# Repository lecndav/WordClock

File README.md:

# Word Clock

This repository contains the source code of my Word Clock and some information about it.

## Order list

* Photo resistor: [Amazon](https://www.amazon.de/DealMux-GL5539-30K-90K-lichtabhängige-Fotowiderstände/dp/B01EZZMLOI/ref=sr_1_1?ie=UTF8&qid=1547571659&sr=8-1&keywords=fotowiderstände)
* LED Strip: [Amazon](https://www.amazon.com/INVOLT-WS2812B-Individually-Addressable-Waterproof/dp/B01N2454TC/ref=pd_cp_86_3?pd_rd_w=VKTPv&pf_rd_p=ef4dc990-a9ca-4945-ae0b-f8d549198ed6&pf_rd_r=ZFWY5T68TFRFS9TXJTRX&pd_rd_r=c3dee8df-1b06-11e9-a4fc-e3295557d665&pd_rd_wg=i8Sjl&pd_rd_i=B01N2454TC&psc=1&refRID=ZFWY5T68TFRFS9TXJTRX)
* Diffusion Foil: [Leuchtbildshop](https://www.leuchtbildshop.net/epages/64015097.sf/de_DE/?ObjectPath=/Shops/64015097/Categories/Diffusionsfolien)
* ESP8266: [Amazon](https://www.amazon.com/gp/product/B07HF44GBT/ref=ppx_yo_dt_b_asin_title_o00_s00?ie=UTF8&psc=1)
* Resistor 330 Ohm
* Resistor 1,2 kOhm
* Solder terminal clamps (2x, 3x)

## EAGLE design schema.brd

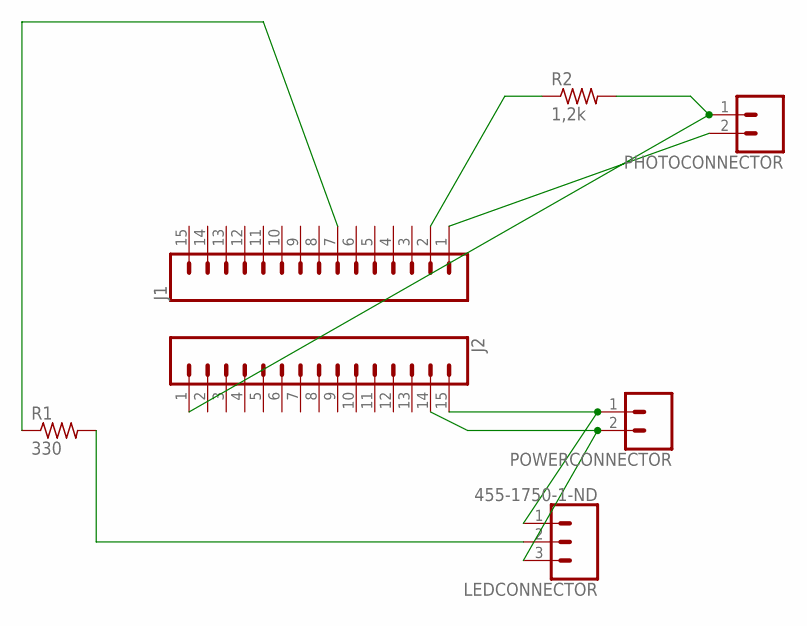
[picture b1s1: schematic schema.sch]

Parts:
J1, J2: CONN_15; 1X15
LEDCONNECTOR: 455-1750-1-ND; 1X03
PHOTOCONNECTOR: CONN_02; 1X02
POWERCONNECTOR: CONN_02; 1X02
R1: 330; 0204V
R2: 1,2k; 0204V

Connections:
unnamed: LEDCONNECTOR.2, R1.2
unnamed: J2.15, LEDCONNECTOR.1, POWERCONNECTOR.1
unnamed: J1.7, R1.1
unnamed: J1.2, R2.1
unnamed: J1.1, PHOTOCONNECTOR.2
unnamed: J2.14, LEDCONNECTOR.3, POWERCONNECTOR.2
unnamed: J2.1, PHOTOCONNECTOR.1, R2.2

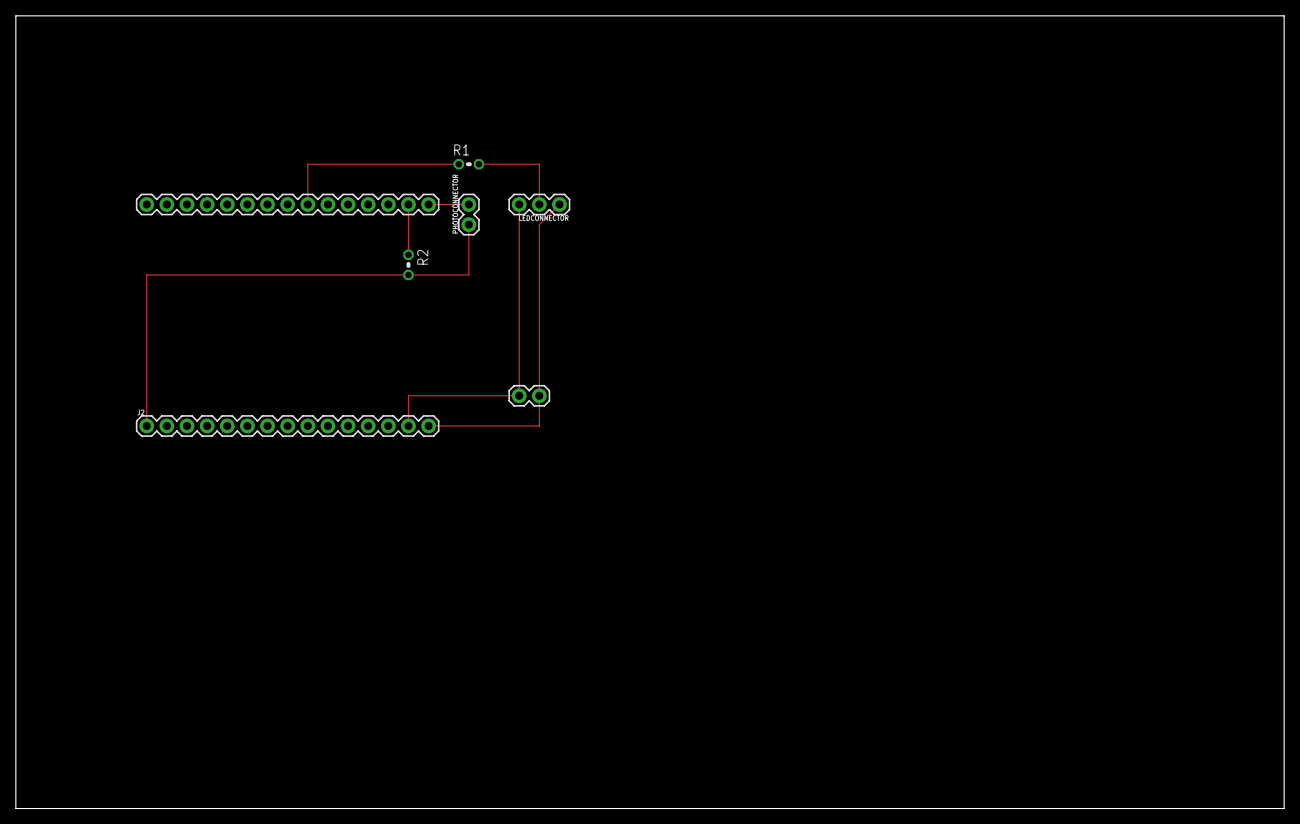
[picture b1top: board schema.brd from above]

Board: 2 copper layers, 160.0 x 100.0 mm, 7 parts (0 on the bottom side), 7 nets.

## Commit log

2019-06-27 added sources
2019-08-02 refactor
2019-08-05 fixed startup flash cousing problems
2019-09-06 better light intensity handling
2021-01-27 switch to sk6812 leds
2021-02-05 removed printlns
2021-02-07 refactored
2021-03-01 adapted light intensity
2021-03-01 removed binary
2021-03-01 fixed time setting
2021-03-18 improved light intensity

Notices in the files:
parts and their libraries:
SparkFun-Connectors: Licensing: Creative Commons ShareAlike 4.0 International - https://creativecommons.org/licenses/by-sa/4.0
